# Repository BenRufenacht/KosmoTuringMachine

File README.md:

# Kosmo Turing Machine

This is the Turing Machine Eurorack module by Tom Whitwell converted into Kosmo format.

Here is the description of the module from Tom Whitwell:

Since it was launched in June 2012, the Turing Machine has become one of the most popular Eurorack DIY projects. It is a random looping sequencer that spits out basslines and melodies. It generates strings of random voltages that can be locked into looping sequences. 
These sequences can be allowed to slip, changing gradually over time. This module was inspired by the long history of shift register pseudorandom synth circuits, including the Triadex Muse, Buchla 266 Source of Uncertainly and Grant Richter’s Noisering.

[This video explains how the Turing Machine works.](https://www.youtube.com/watch?v=Le26BIqB8Y8)  

The 2016 revised Turing Machine has many improvements:  
- Rotary loop length switch 
- Pulse out
- Two boards, includes Backpack circuit to drive expanders (compatible with old Music Thing expanders)  
- Easier to build: a larger PCB in the same width, clock and noise circuits are more robust
- Noise level trimmer & reduced voltage in noise circuit to make circuit more robust with different noise transistors 
- Compatible with existing expanders 

[Schematic](https://github.com/TomWhitwell/TuringMachine/blob/master/Collateral/PDF%20Schematics/TuringMachine2_Schematic_May2016.pdf)

Status:   
July 2022 - Boards were manufactured and tested. Updates have been made to the main board and panel, but these updates have not been tested.

License:  
[CC-BY-SA](https://creativecommons.org/licenses/by-sa/3.0/)

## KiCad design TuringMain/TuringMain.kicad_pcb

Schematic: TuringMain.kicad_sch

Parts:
AND_1, AND_2: 4081; DIL14
BUFFER1, BUFFER2: 4050; DIL16
C1, C2, C3, C4, C7, C8, C13, C14, C16, C19, C21, C22, C26, C27: 100n; C050-024X044
C5, C6: 10uf; CP_Radial_D6.3mm_P2.50mm
C9: 10n; C050-024X044
C10, C11, C18: 0.47uf; C050-035X075
C12, C17, C20, C23, C24, C25: 1n; C050-024X044
C15: 330pf; C050-024X044
CHANGE1: 50k; Potentiometer_Alpha_RD901F-40-00D_Single_Vertical_centered
CLK1: LED5MM; LED_D5.0mm
CLOCK1: THONKICONNNEW; Jack_6.35mm_PJ_629HAN
CV_IN1: THONKICONNNEW; Jack_6.35mm_PJ_629HAN
CV_OUT1: THONKICONNNEW; Jack_6.35mm_PJ_629HAN
D2: 1N4148; DO35-7
GATES1: MA08-2; IDC-Header_2x08_P2.54mm_Vertical
IC1: TL072P; DIL08
IC2, IC3: 78L09; TO-92_Inline_Wide
J1: Conn_01x10_Male; PinHeader_1x10_P2.54mm_Vertical
J2: Conn_01x10_Female; PinSocket_1x10_P2.54mm_Vertical
L1, L2: BL01RN1A
LENGTH1: ALPS-SRBV
NOISE-OUT1: THONKICONNNEW; Jack_6.35mm_PJ_629HAN
PULS1: LED5MM; LED_D5.0mm
PULSES1: MA08-2; IDC-Header_2x08_P2.54mm_Vertical
PULSE_OUT1: THONKICONNNEW; Jack_6.35mm_PJ_629HAN
R1, R4, R6, R8, R13, R14, R15, R16, R17, R21: 2.2k; R_Axial_DIN0207_L6.3mm_D2.5mm_P10.16mm_Horizontal
R2, R9: 15k; R_Axial_DIN0207_L6.3mm_D2.5mm_P10.16mm_Horizontal
R3: 68k; R_Axial_DIN0207_L6.3mm_D2.5mm_P10.16mm_Horizontal
R5: 51k; R_Axial_DIN0207_L6.3mm_D2.5mm_P10.16mm_Horizontal
R7, R31: 470k; R_Axial_DIN0207_L6.3mm_D2.5mm_P10.16mm_Horizontal
R10, R11, R22, R25, R29: 100k; R_Axial_DIN0207_L6.3mm_D2.5mm_P10.16mm_Horizontal
R12, R23, R30, R33, R34, R35, R36, R37, R38, R39: 10k; R_Axial_DIN0207_L6.3mm_D2.5mm_P10.16mm_Horizontal
R18, R19, R32: 1k; R_Axial_DIN0207_L6.3mm_D2.5mm_P10.16mm_Horizontal
R20: 3.3k; R_Axial_DIN0207_L6.3mm_D2.5mm_P10.16mm_Horizontal
R24: 47k; R_Axial_DIN0207_L6.3mm_D2.5mm_P10.16mm_Horizontal
R26: 5.1k; R_Axial_DIN0207_L6.3mm_D2.5mm_P10.16mm_Horizontal
R27, R28: 1.6k; R_Axial_DIN0207_L6.3mm_D2.5mm_P10.16mm_Horizontal
SCALE1: 50k; Potentiometer_Alpha_RD901F-40-00D_Single_Vertical_centered
SHIFTREG_EXT1: 4015; DIL16
SHIFTREG_MAIN1: 4015; DIL16
SV1: 10_PIN_HEADER; Power_Header
SWITCH_IC1: 4016; DIL14
T1: 2N3904; TO-92_Inline_Wide
TL431: TL431CLP; TO-92_Inline_Wide
U1: TL074_; DIL14
U$2: DAC0800; DIL16
UNK1, UNK2, UNK3, UNK4, UNK5, UNK6, UNK7, UNK8: LED5MM; LED_D5.0mm
VR1: 1m; Potentiometer_Bourns_3296W_Vertical_screw_centered
WRITE1: T-80-T-SPDT-ON-OFF-ON; SPDT-toggle-switch-1M-series

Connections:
/+12V: AND_1.14 (VDD), AND_2.14 (VDD), C1.1, C2.1, C3.1, C4.1, C5.1, C7.2, C13.1, C19.2, C26.2, GATES1.15, GATES1.16, IC1.8 (V+), IC2.3 (VI), IC3.3 (VI), L1.2, PULSES1.15, PULSES1.16, R3.1, R20.1, R23.2, R29.1, R33.2, R34.2, SHIFTREG_EXT1.16 (VDD), SHIFTREG_MAIN1.16 (VDD), SWITCH_IC1.14 (VDD), U1.4 (V+), U$2.13 (V+), WRITE1.1 (O)
/+12V_INLET: L1.1, SV1.9 (+12V), SV1.10 (+12V)
/-12V: C6.2, C8.1, C9.2, C14.2, C27.2, GATES1.11, GATES1.12, IC1.4 (V-), L2.2, PULSES1.11, PULSES1.12, R35.2, U1.11 (V-), U$2.3 (V-)
/-12V_INLET: L2.1, SV1.1 (-12V), SV1.2 (-12V)
/B1: AND_1.1 (I0), BUFFER1.9 (I), LENGTH1.F (6), R38.1, SHIFTREG_MAIN1.2 (QD), U$2.5 (B1-MSB), UNK1.2 (A)
/B2: AND_1.12 (I0), BUFFER1.11 (I), SHIFTREG_MAIN1.11 (QC), U$2.6 (B2), UNK2.2 (A)
/B3: AND_1.5 (I0), BUFFER1.7 (I), LENGTH1.E (5), SHIFTREG_MAIN1.12 (QB), U$2.7 (B3), UNK3.2 (A)
/B4: AND_1.8 (I0), BUFFER1.5 (I), LENGTH1.D (4), SHIFTREG_MAIN1.13 (QA), U$2.8 (B4), UNK4.2 (A)
/B5: AND_2.12 (I0), BUFFER2.11 (I), LENGTH1.C (3), R37.1, SHIFTREG_MAIN1.10 (QD), U$2.9 (B5), UNK5.2 (A)
/B6: AND_2.8 (I0), BUFFER2.9 (I), LENGTH1.B (2), SHIFTREG_MAIN1.3 (QC), U$2.10 (B6), UNK6.2 (A)
/B7: AND_2.5 (I0), BUFFER2.7 (I), LENGTH1.A (1), SHIFTREG_MAIN1.4 (QB), U$2.11 (B7), UNK7.2 (A)
/B8: AND_2.1 (I0), BUFFER2.5 (I), SHIFTREG_MAIN1.5 (QA), U$2.12 (B8-LSB), UNK8.2 (A)
/BUFFCLK: AND_1.2 (I1), AND_1.6 (I1), AND_1.9 (I1), AND_1.13 (I1), BUFFER2.2 (O), PULSES1.9, PULSES1.10
/BUFFCLK2: AND_2.2 (I1), AND_2.6 (I1), AND_2.9 (I1), AND_2.13 (I1), BUFFER1.2 (O), GATES1.9, GATES1.10
/CLOCK: BUFFER1.3 (I), BUFFER2.3 (I), D2.C, R7.1, R12.1, R13.1, SHIFTREG_EXT1.1 (CLK), SHIFTREG_EXT1.9 (CLK), SHIFTREG_MAIN1.1 (CLK), SHIFTREG_MAIN1.9 (CLK)
/CLOCK_IN: J1.2, R2.1
/CV_IN: J1.4, R5.1
/CV_OUT: CV_OUT1.T, J1.8, SCALE1.2
/END_OF_LOOP: LENGTH1.COM (A), LENGTH1.COM2 (A), SWITCH_IC1.1 (A), SWITCH_IC1.5 (C)
/GATE1: BUFFER2.4 (O), GATES1.1
/GATE2: BUFFER2.6 (O), GATES1.2
/GATE3: BUFFER2.10 (O), GATES1.3
/GATE4: BUFFER2.12 (O), GATES1.4
/GATE5: BUFFER1.4 (O), GATES1.5
/GATE6: BUFFER1.6 (O), GATES1.6
/GATE7: BUFFER1.12 (O), GATES1.7
/GATE8: GATES1.8
/LOOP_CTRL: IC1.2 (-IN), R5.2, R22.2, R24.1
/NOISE: C11.2, IC1.5 (+IN), R11.2, R19.2
/NOISE_OUT: J1.6, R19.1
/PULSE1: AND_2.3 (O), BUFFER1.14 (I), PULSES1.1
/PULSE2: AND_2.4 (O), PULSES1.2
/PULSE3: AND_2.10 (O), PULSES1.3
/PULSE4: AND_2.11 (O), PULSES1.4
/PULSE5: AND_1.10 (O), PULSES1.5
/PULSE6: AND_1.4 (O), PULSES1.6
/PULSE7: AND_1.11 (O), PULSES1.7
/PULSE8: AND_1.3 (O), PULSES1.8
/PULSE_OUT: BUFFER1.15 (O), J1.7, R17.1
/START_OF_LOOP: C20.2, R18.2, R36.1, SHIFTREG_MAIN1.7 (D)
/STEP_12: C25.2, LENGTH1.G (7), R39.2, SHIFTREG_EXT1.15 (D)
/STEP_16: LENGTH1.H (8), SHIFTREG_EXT1.2 (QD)
GND: AND_1.7 (VSS), AND_2.7 (VSS), BUFFER1.8 (VSS), BUFFER2.8 (VSS), BUFFER2.14 (I), C1.2, C2.2, C3.2, C4.2, C5.2, C6.1, C7.1, C8.2, C13.2, C14.1, C15.1, C16.1, C19.1, C20.1, C21.1, C22.1, C23.1, C24.1, C25.1, C26.1, C27.1, CLK1.1 (K), CLOCK1.S, CV_IN1.S, CV_OUT1.S, GATES1.13, GATES1.14, IC1.3 (+IN), IC2.2 (GND), IC3.2 (GND), J1.1, J1.10, J2.1, J2.10, NOISE-OUT1.S, PULS1.1 (K), PULSES1.13, PULSES1.14, PULSE_OUT1.S, R1.2, R4.2, R6.2, R8.2, R9.1, R10.1, R11.1, R12.2, R14.1, R15.1, R16.1, R21.1, R27.1, SCALE1.1, SHIFTREG_EXT1.6 (RES), SHIFTREG_EXT1.8 (VSS), SHIFTREG_EXT1.14 (RES), SHIFTREG_MAIN1.6 (RES), SHIFTREG_MAIN1.8 (VSS), SHIFTREG_MAIN1.14 (RES), SV1.3 (GND), SV1.4 (GND), SV1.5 (GND), SV1.6 (GND), SV1.7 (GND), SV1.8 (GND), SWITCH_IC1.3 (B), SWITCH_IC1.7 (VSS), SWITCH_IC1.9 (B), T1.2 (B), TL431.2 (A), U1.3 (+IN), U1.10 (+IN), U1.12 (+IN), U$2.1 (VLC), U$2.2 (IOUT), WRITE1.3 (S)
unnamed: BUFFER1.1 (VDD), C21.2, IC2.1 (VO)
unnamed: BUFFER2.1 (VDD), C22.2, IC3.1 (VO)
unnamed: C9.1, U$2.16 (COMP)
unnamed: C10.1, R30.1
unnamed: C10.2, R29.2, T1.1 (E)
unnamed: C11.1, C12.2, U1.14 (OUT), VR1.2, VR1.3
unnamed: C12.1, R32.1, U1.13 (-IN), VR1.1
unnamed: C15.2, R2.2, R7.2, R10.2, U1.5 (+IN)
unnamed: C16.2, R3.2, R9.2, U1.6 (-IN)
unnamed: C17.1, R26.1, U1.2 (-IN), U$2.4 (IOUTB)
unnamed: C17.2, R26.2, SCALE1.3, U1.1 (OUT)
unnamed: C18.1, R31.1, U1.8 (OUT)
unnamed: C18.2, R32.2
unnamed: C23.2, R37.2, SHIFTREG_MAIN1.15 (D)
unnamed: C24.2, R38.2, SHIFTREG_EXT1.7 (D)
unnamed: CHANGE1.1, R35.1
unnamed: CHANGE1.2, R22.1
unnamed: CHANGE1.3, R23.1
unnamed: CLK1.2 (A), R13.2
unnamed: CLOCK1.T, J2.2
unnamed: CV_IN1.T, J2.4
unnamed: D2.A, U1.7 (OUT)
unnamed: IC1.1 (OUT), IC1.6 (-IN), R24.2
unnamed: IC1.7 (OUT), R25.2
unnamed: J2.6, NOISE-OUT1.T
unnamed: J2.7, PULSE_OUT1.T
unnamed: PULS1.2 (A), R17.2
unnamed: R1.1, UNK8.1 (K)
unnamed: R4.1, UNK7.1 (K)
unnamed: R6.1, UNK6.1 (K)
unnamed: R8.1, UNK5.1 (K)
unnamed: R14.2, UNK4.1 (K)
unnamed: R15.2, UNK3.1 (K)
unnamed: R16.2, UNK2.1 (K)
unnamed: R18.1, WRITE1.2
unnamed: R20.2, R28.2, TL431.1 (REF), TL431.3 (K)
unnamed: R21.2, UNK1.1 (K)
unnamed: R25.1, SWITCH_IC1.6 (C), SWITCH_IC1.13 (C)
unnamed: R27.2, U$2.15 (VREF-)
unnamed: R28.1, U$2.14 (VREF+)
unnamed: R30.2, R31.2, U1.9 (-IN)
unnamed: R33.1, SWITCH_IC1.8 (A), SWITCH_IC1.12 (C)
unnamed: R34.1, SWITCH_IC1.4 (A), SWITCH_IC1.11 (A)
unnamed: R36.2, SWITCH_IC1.2 (B), SWITCH_IC1.10 (B)
unnamed: R39.1, SHIFTREG_EXT1.10 (QD)

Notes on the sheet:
Shift register loop
Length steps: 16 = step_16 12 = step_12 8 = B1 6 = B3 5 = B4 4 = B5 3 = B6 2 = B7
Randomised invert/loop switching
/Users/aash/Dropbox/Electronics/~{MODULAR/design/logo} copy.bmp
DAC
NB: Bit numbers are reversed at this point: Bit8 = first bit (left hand LED on main module) becomes Pulse1 (Top output on expanders)
Clock input
Noise Generator

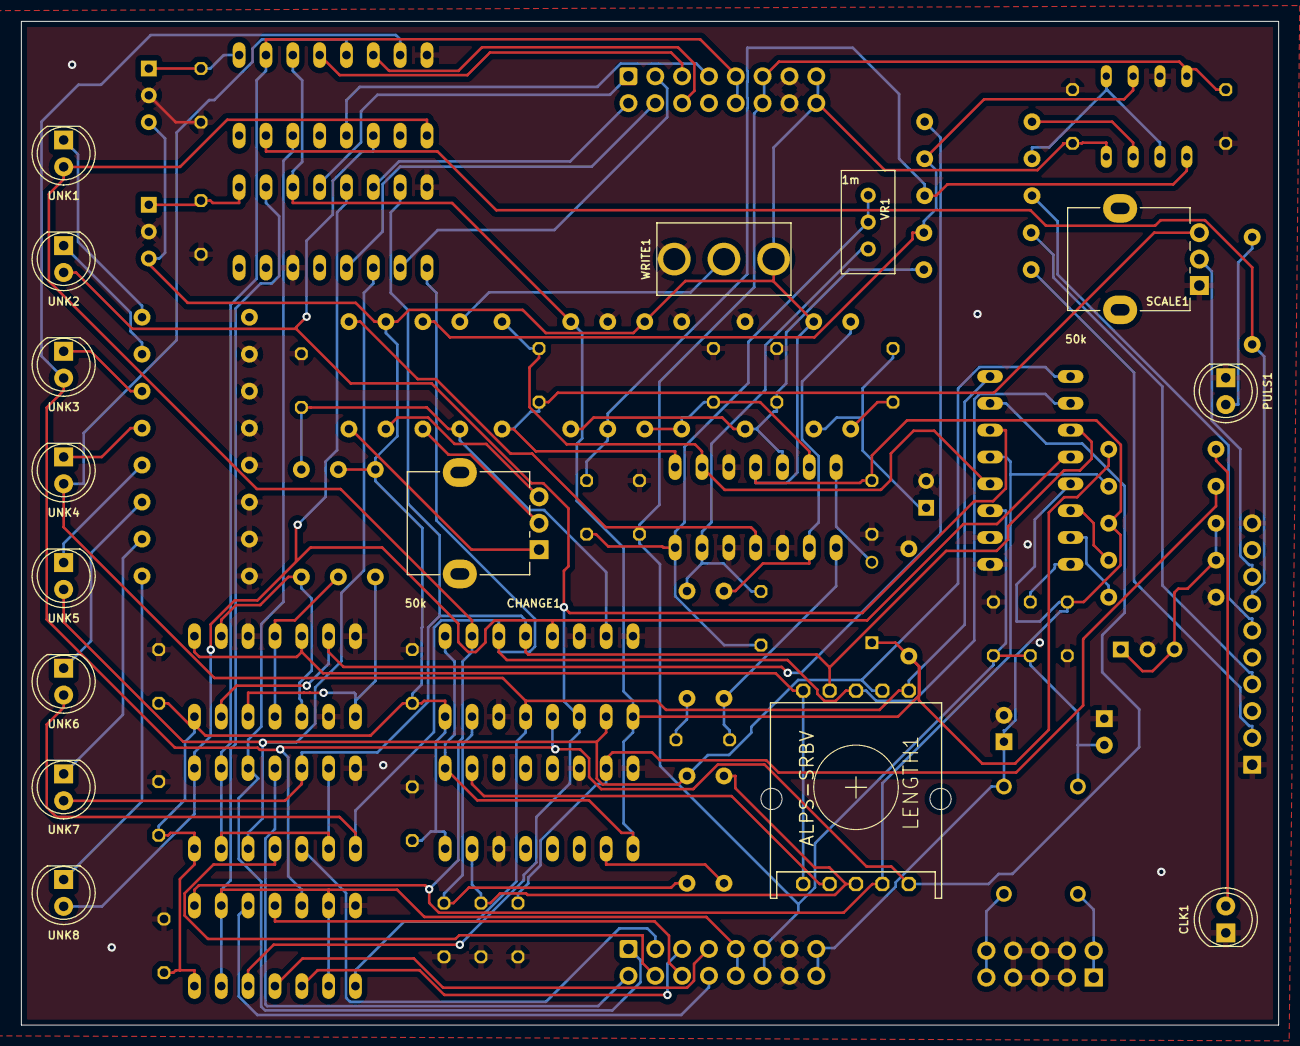
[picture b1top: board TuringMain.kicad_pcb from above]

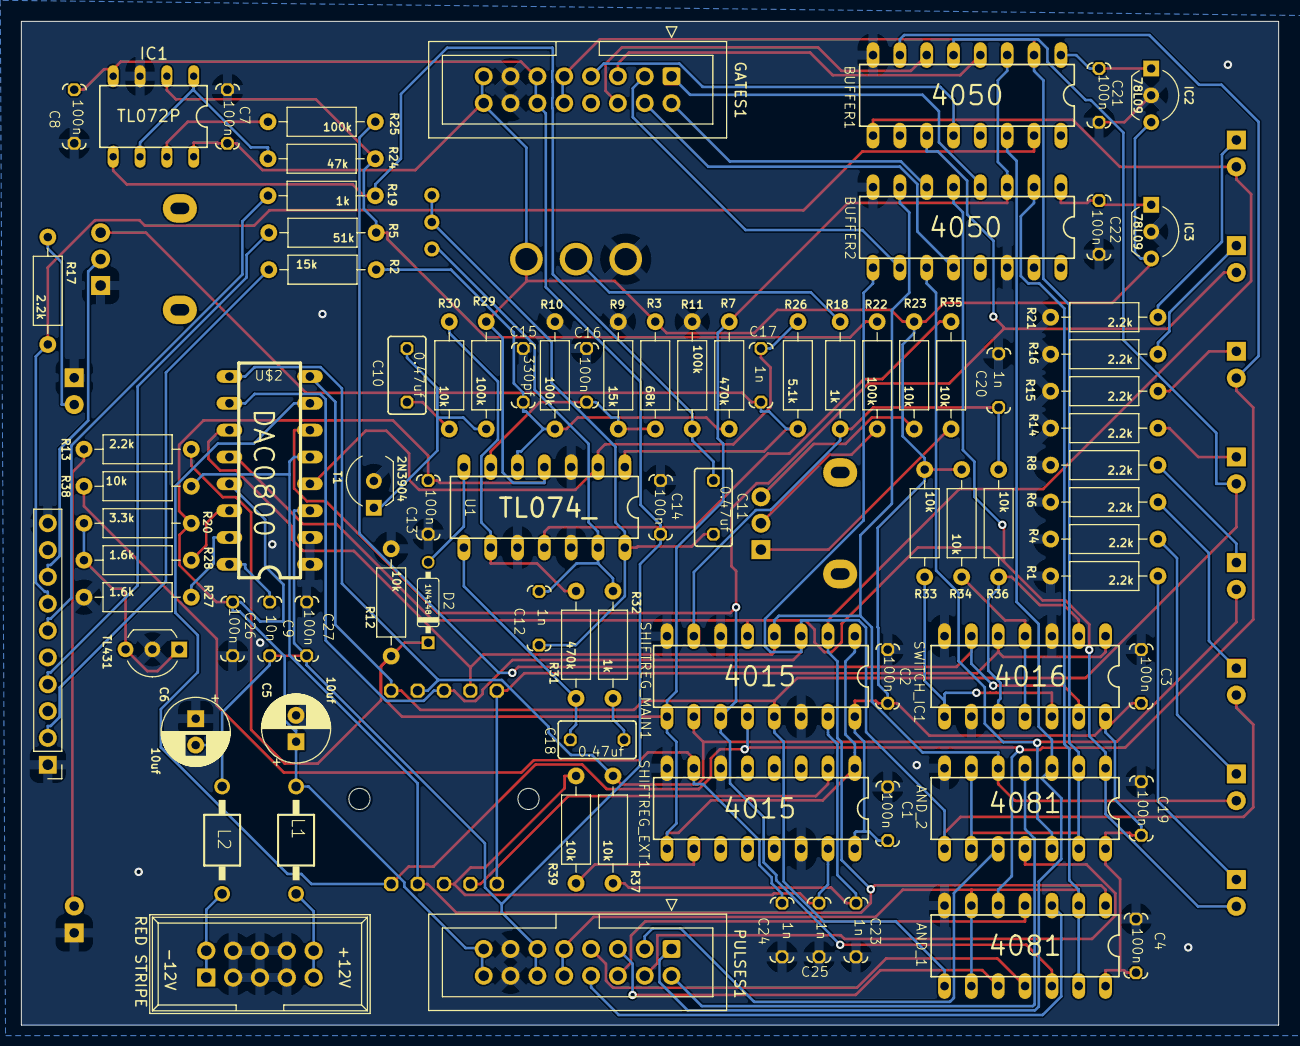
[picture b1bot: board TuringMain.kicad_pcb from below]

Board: 2 copper layers, 119.0 x 95.0 mm, 102 parts (87 on the bottom side), 83 nets.

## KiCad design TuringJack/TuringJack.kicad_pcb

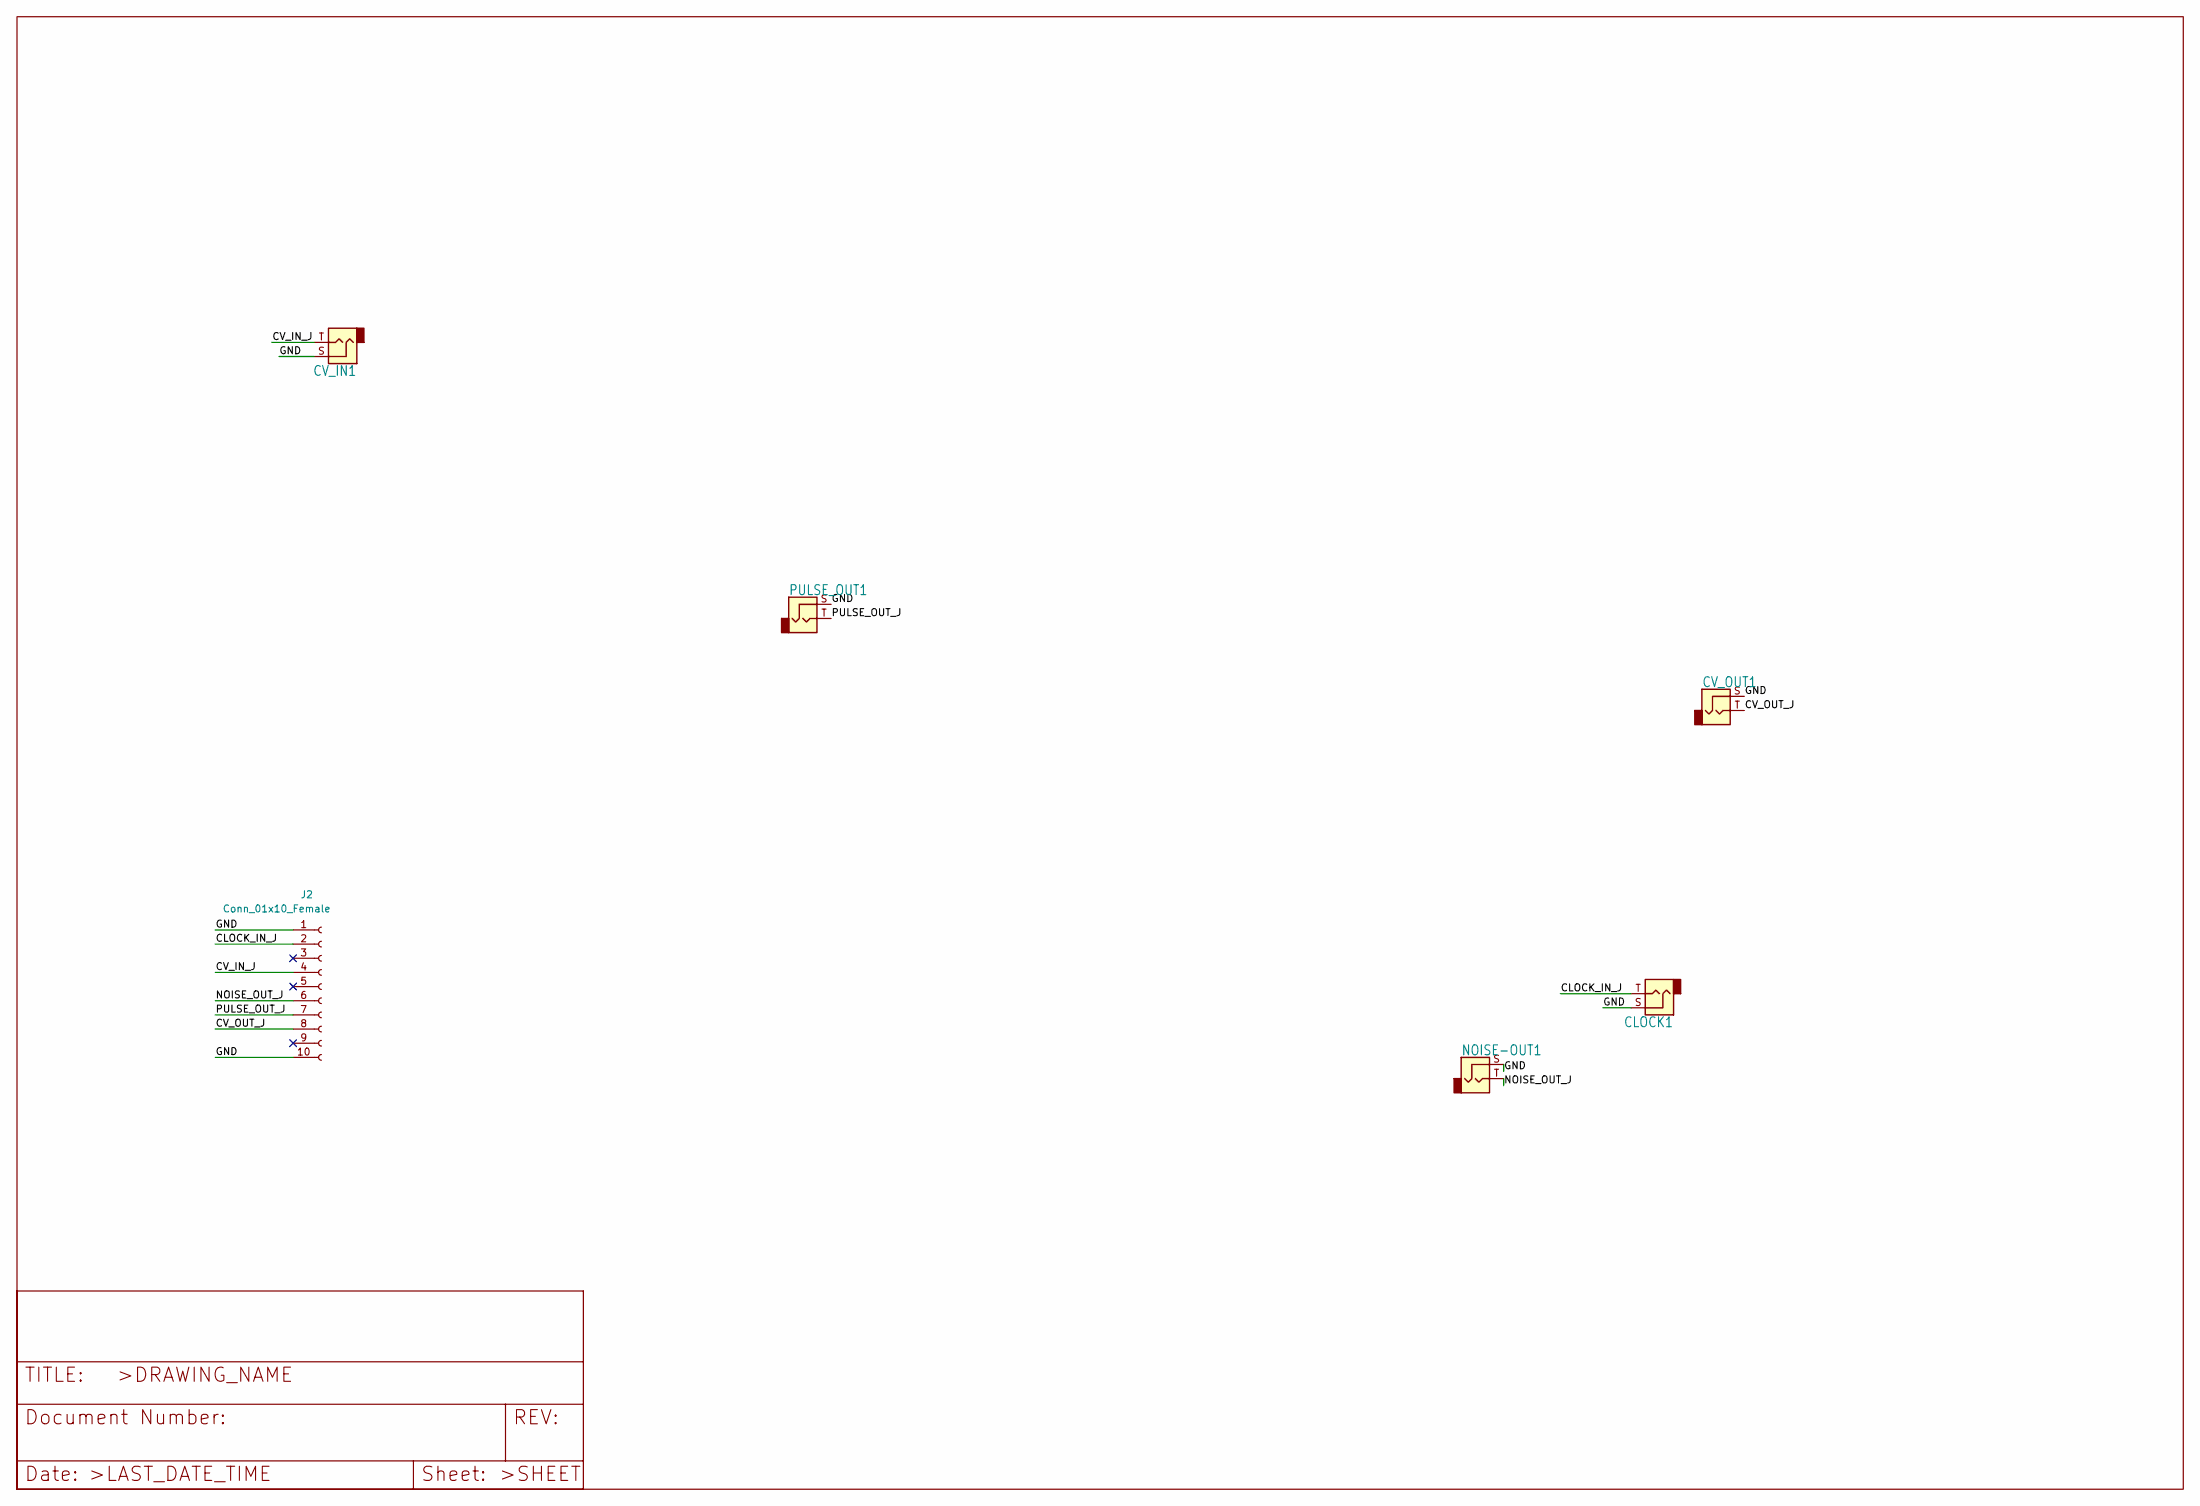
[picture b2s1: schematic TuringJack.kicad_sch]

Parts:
CLOCK1: THONKICONNNEW; Jack_6.35mm_PJ_629HAN
CV_IN1: THONKICONNNEW; Jack_6.35mm_PJ_629HAN
CV_OUT1: THONKICONNNEW; Jack_6.35mm_PJ_629HAN
J2: Conn_01x10_Female; PinSocket_1x10_P2.54mm_Vertical
NOISE-OUT1: THONKICONNNEW; Jack_6.35mm_PJ_629HAN
PULSE_OUT1: THONKICONNNEW; Jack_6.35mm_PJ_629HAN

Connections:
/CLOCK_IN_J: CLOCK1.T, J2.2
/CV_IN_J: CV_IN1.T, J2.4
/CV_OUT_J: CV_OUT1.T, J2.8
/GND: CLOCK1.S, CV_IN1.S, CV_OUT1.S, J2.1, J2.10, NOISE-OUT1.S, PULSE_OUT1.S
/NOISE_OUT_J: J2.6, NOISE-OUT1.T
/PULSE_OUT_J: J2.7, PULSE_OUT1.T

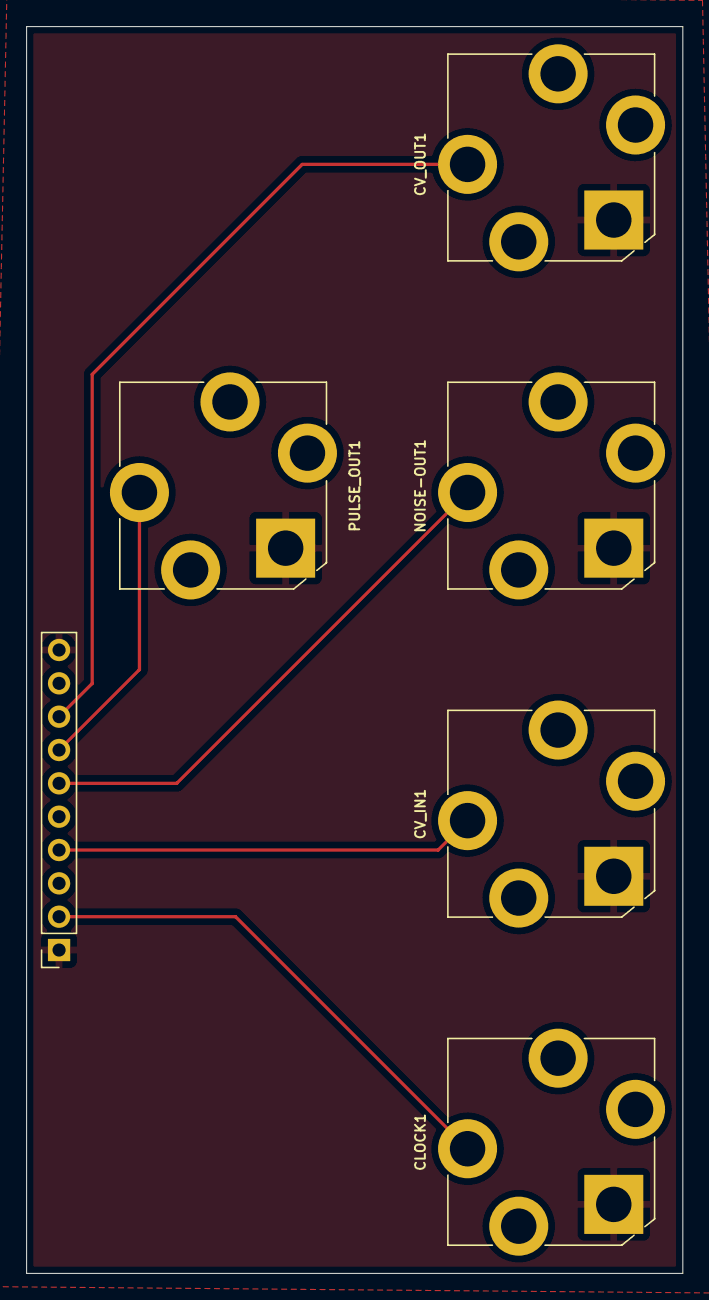
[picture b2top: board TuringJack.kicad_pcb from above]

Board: 2 copper layers, 50.0 x 95.0 mm, 6 parts (0 on the bottom side), 6 nets.

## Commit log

2022-06-05 Initial Upload
2022-06-05 Main Board Updates
    Fixed GND errors and flipped expansion headers to back of the board
2022-06-09 Updated Panel Graphics
2022-06-10 Manufacturing Updates
2022-07-14 Manufacturing Updates
    Rotary Switch Panel Drill Corrected
    Panel Graphics Changed (Name changed from Turing Machine to The Halting Problem)
    Updated silkscreen on mainboard with circuit corrections and component values.
2022-07-14 Added Image
2022-07-14 Gerber zip
2022-07-31 Minor Main Board updates

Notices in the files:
TuringJack/TuringJack.kicad_pcb:
February 2016 CC-BY-SA
